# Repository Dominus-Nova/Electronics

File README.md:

# Electronics
a collection of my kicad electronics projects

general note is that this is my shit, its only public so my friends can see it without a github account
oh, new folder contains a currently broken project, it has its own repo but it broke

test^2

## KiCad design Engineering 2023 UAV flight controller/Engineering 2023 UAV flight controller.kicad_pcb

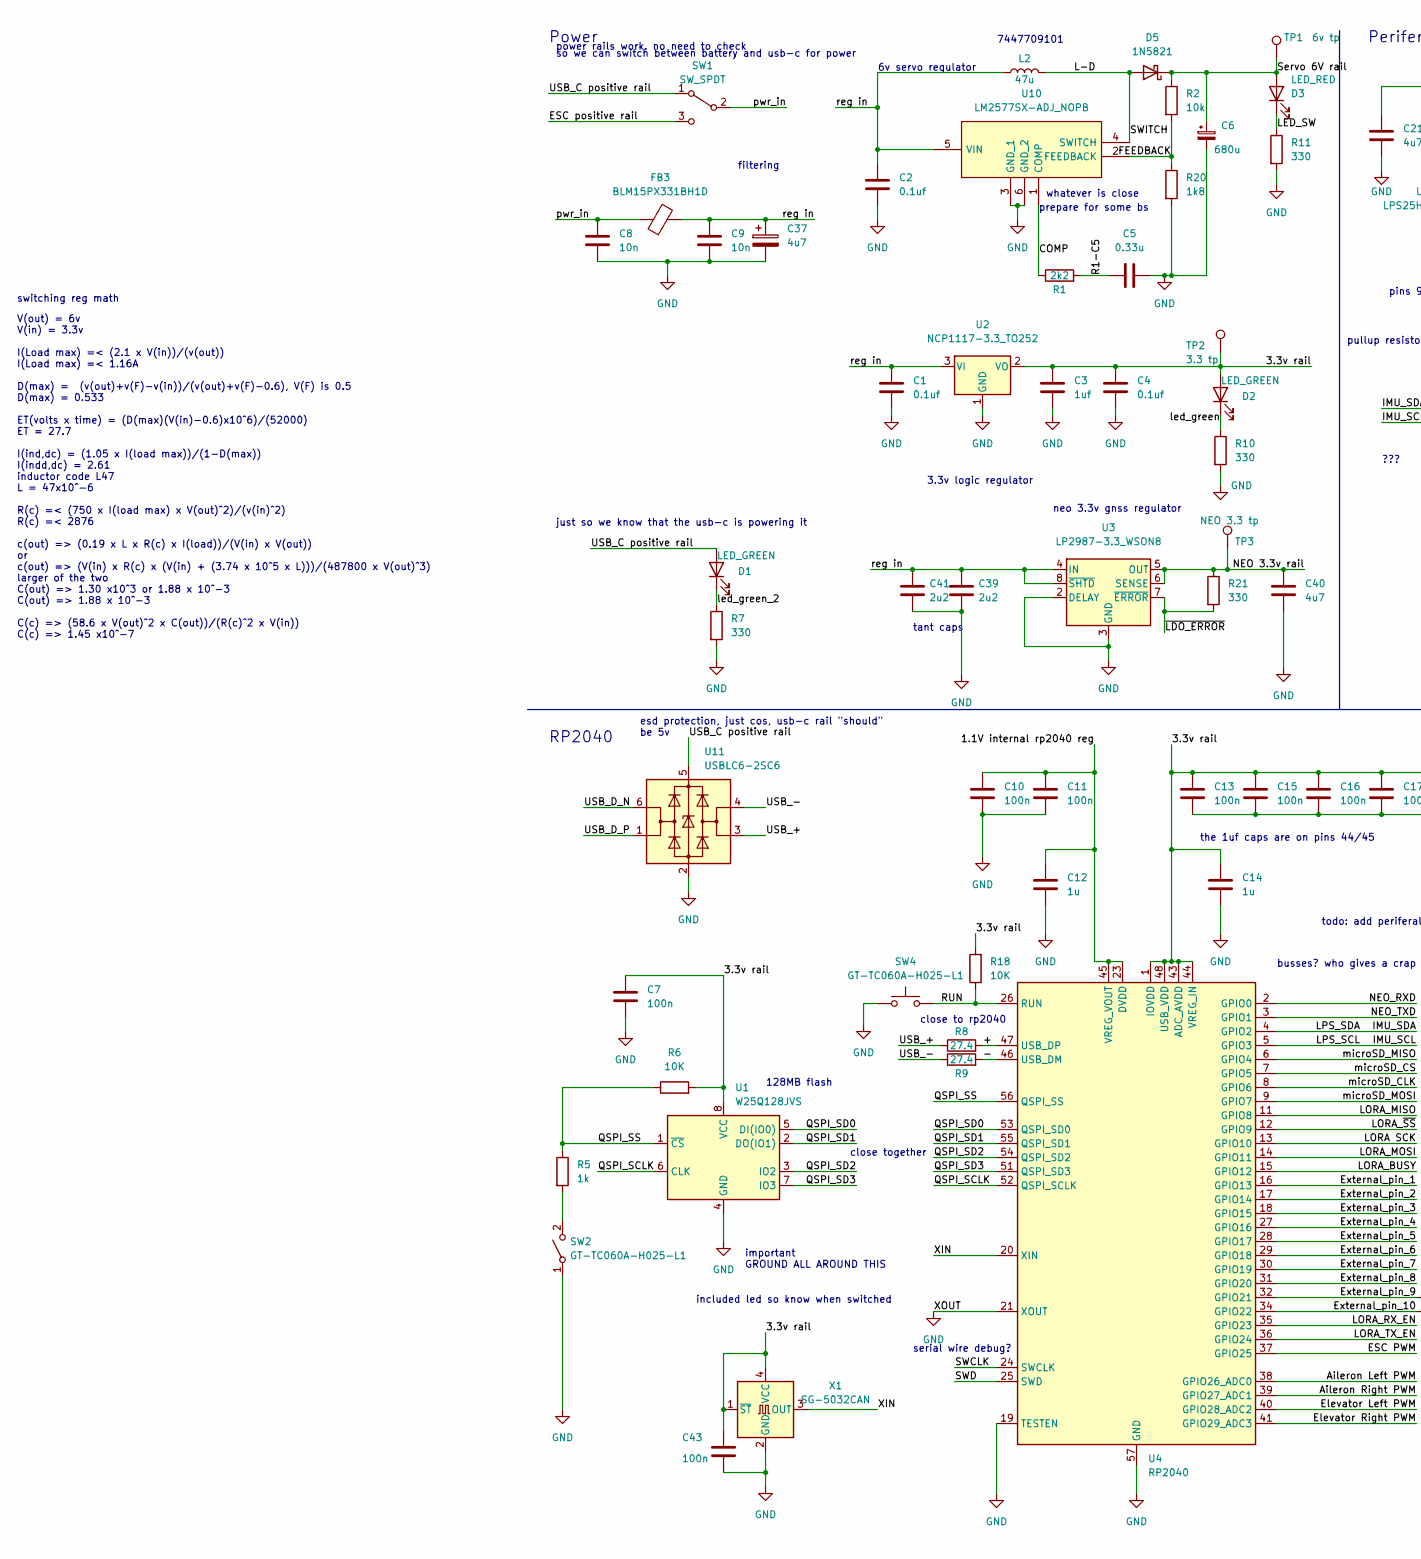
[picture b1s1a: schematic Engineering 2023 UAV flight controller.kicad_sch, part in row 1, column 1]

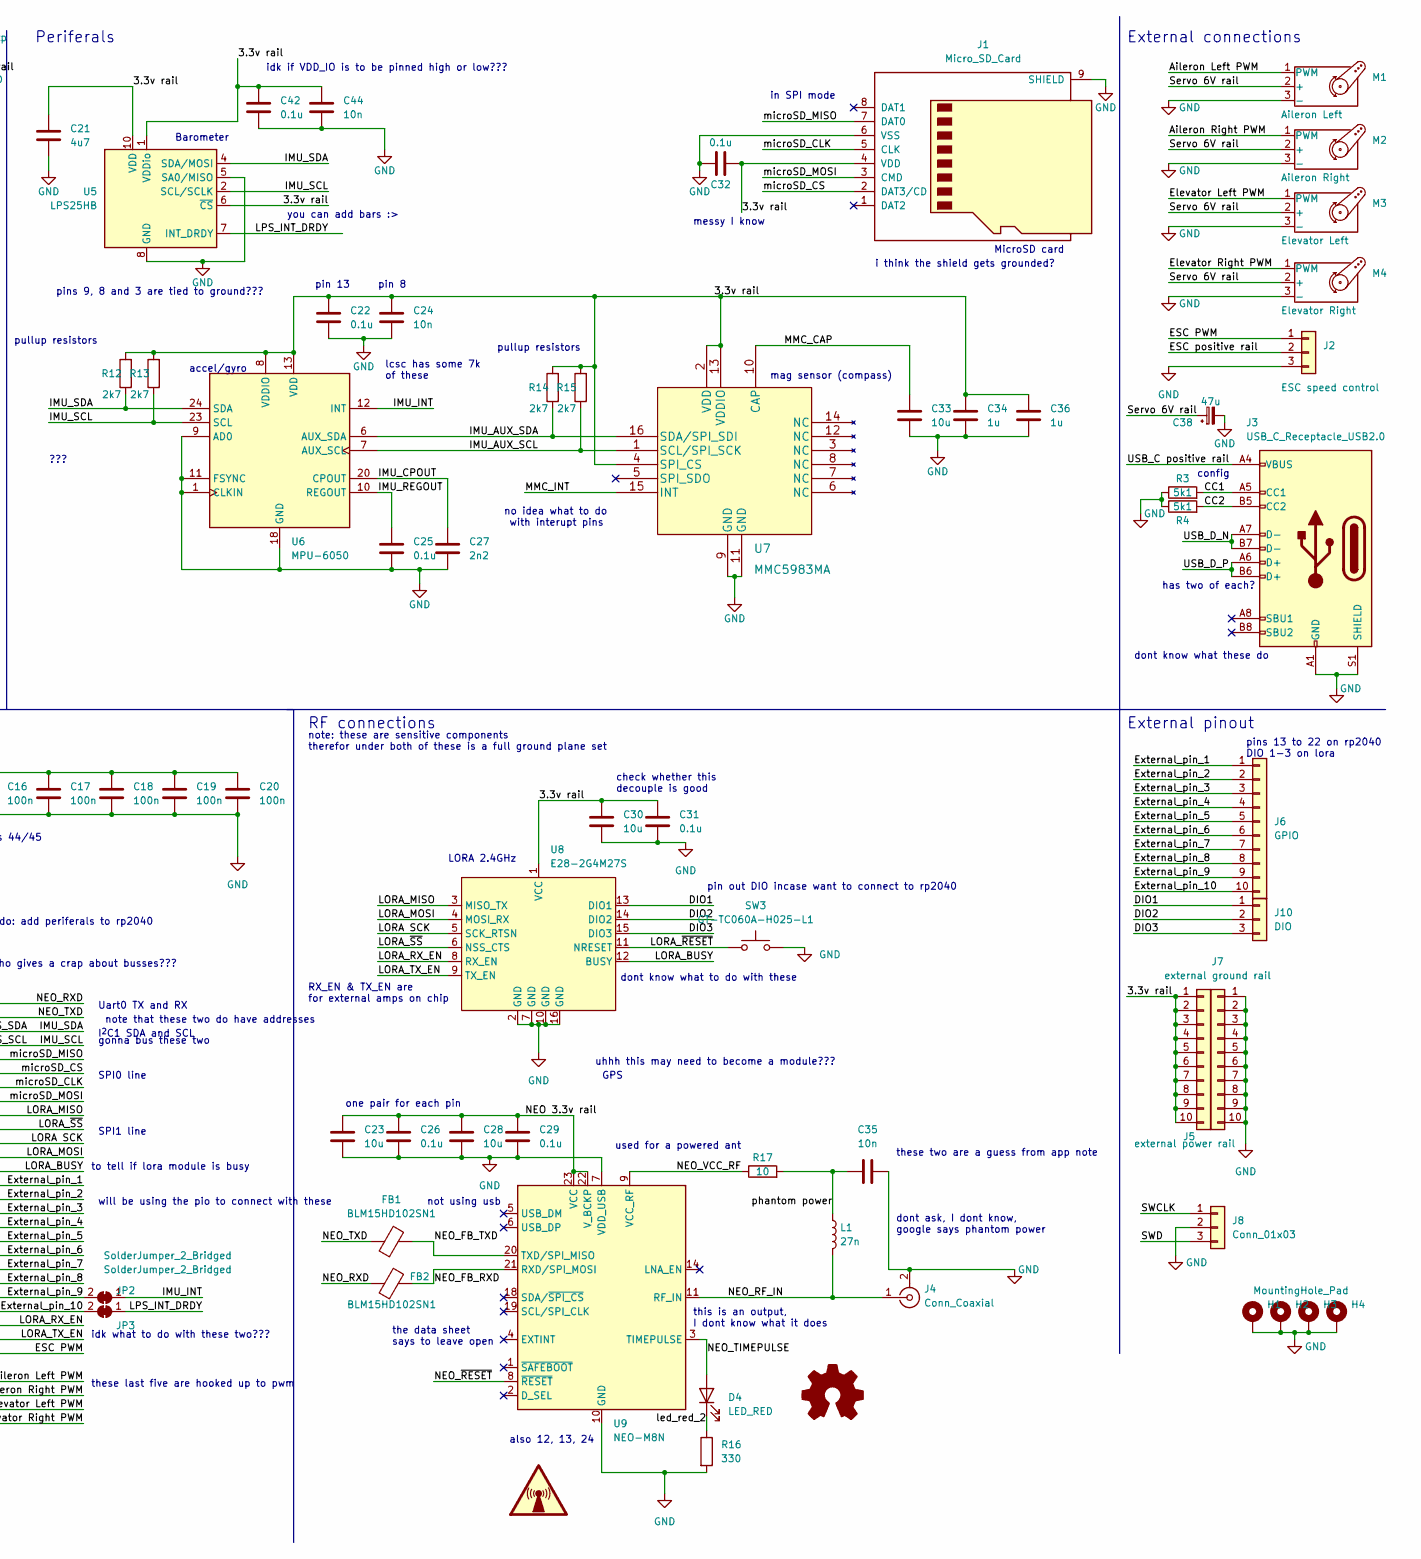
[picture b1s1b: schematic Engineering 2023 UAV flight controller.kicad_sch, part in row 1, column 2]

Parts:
C1, C2, C4: 0.1uf; C_0603_1608Metric
C3: 1uf; C_0603_1608Metric
C5: 0.33u; C_0603_1608Metric
C6: 680u; CP_Elec_8x6.5
C7, C10, C11, C13, C15, C16, C17, C18, C19, C20, C43: 100n; C_0603_1608Metric
C8, C9, C24, C35, C44: 10n; C_0603_1608Metric
C12, C14, C34, C36: 1u; C_0603_1608Metric
C21, C40: 4u7; C_0603_1608Metric
C22, C25, C26, C29, C31, C32, C42: 0.1u; C_0603_1608Metric
C23, C28, C30, C33: 10u; C_0603_1608Metric
C27: 2n2; C_0603_1608Metric
C37: 4u7; CP_Elec_5x3
C38: 47u; CP_Elec_5x3
C39, C41: 2u2; C_0603_1608Metric
D1, D2: LED_GREEN; LED_0603_1608Metric
D3, D4: LED_RED; LED_0603_1608Metric
D5: 1N5821; D_SMC
FB1, FB2: BLM15HD102SN1; L_0402_1005Metric_Pad0.77x0.64mm_HandSolder
FB3: BLM15PX331BH1D; L_0402_1005Metric_Pad0.77x0.64mm_HandSolder
H1, H2, H3, H4: MountingHole_Pad; MountingHole_3.2mm_M3_Pad_Via
J1: Micro_SD_Card; microSD_HC_Hirose_DM3D-SF
J2: ESC speed control; PinHeader_1x03_P2.54mm_Vertical
J3: USB_C_Receptacle_USB2.0; USB_C_Receptacle_JAE_DX07S016JA1R1500
J4: Conn_Coaxial; SMA_Amphenol_901-143_Horizontal
J5: external power rail; PinHeader_1x10_P2.54mm_Vertical
J6: GPIO; PinHeader_1x10_P2.54mm_Vertical
J7: external ground rail; PinHeader_1x10_P2.54mm_Vertical
J8: Conn_01x03; PinHeader_1x03_P2.54mm_Vertical
J10: DIO; PinHeader_1x03_P2.54mm_Vertical
JP2, JP3: SolderJumper_2_Bridged; SolderJumper-2_P1.3mm_Bridged_RoundedPad1.0x1.5mm
L1: 27n; L_0603_1608Metric
L2: 47u; L_Wuerth_WE-PD-Typ-LS
M1: Aileron Left; PinHeader_1x03_P2.54mm_Vertical
M2: Aileron Right; PinHeader_1x03_P2.54mm_Vertical
M3: Elevator Left; PinHeader_1x03_P2.54mm_Vertical
M4: Elevator Right; PinHeader_1x03_P2.54mm_Vertical
R1: 2k2; R_0603_1608Metric
R2: 10k; R_0603_1608Metric
R3, R4: 5k1; R_0603_1608Metric
R5: 1k; R_0603_1608Metric
R6, R18: 10K; R_0603_1608Metric
R7, R10, R11, R16, R21: 330; R_0603_1608Metric
R8, R9: 27.4; R_0603_1608Metric
R12, R13, R14, R15: 2k7; R_0603_1608Metric
R17: 10; R_0603_1608Metric
R20: 1k8; R_0603_1608Metric
SW1: SW_SPDT; SW_SPDT_CK-JS102011SAQN
SW2, SW3, SW4: GT-TC060A-H025-L1; SW_SPST_CK_RS282G05A3
TP1: 6v tp; TestPoint_Pad_D2.5mm
TP2: 3.3 tp; TestPoint_Pad_D2.5mm
TP3: NEO 3.3 tp; TestPoint_Pad_D2.5mm
U1: W25Q128JVS; SOIC-8_5.23x5.23mm_P1.27mm
U2: NCP1117-3.3_TO252; TO-252-2
U3: LP2987-3.3_WSON8; WSON-8-1EP_4x4mm_P0.8mm_EP2.2x3mm
U4: RP2040; QFN-56-1EP_7x7mm_P0.4mm_EP3.2x3.2mm
U5: LPS25HB; ST_HLGA-10_2.5x2.5mm_P0.6mm_LayoutBorder3x2y
U6: MPU-6050; InvenSense_QFN-24_4x4mm_P0.5mm
U7: MMC5983MA
U8: E28-2G4M27S
U9: NEO-M8N; ublox_NEO
U10: LM2577SX-ADJ_NOPB; TO-263-5_TabPin3; Manufacturer_Part_Number LM2577SX-ADJ/NOPB; Mouser Part Number 926-LM2577SXADJNOPB
U11: USBLC6-2SC6; SOT-23-6
X1: SG-5032CAN; Oscillator_SMD_SeikoEpson_SG8002LB-4Pin_5.0x3.2mm

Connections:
/1.1V internal rp2040 reg: C10.1, C11.1, C12.1, U4.23 (DVDD), U4.45 (VREG_VOUT), U4.50 (DVDD)
/3.3v rail: C3.1, C4.1, C7.1, C13.1, C14.1, C15.1, C16.1, C17.1, C18.1, C19.1, C20.1, C21.2, C22.2, C24.2, C30.1, C31.1, C32.1, C34.2, C36.2, C42.2, C43.1, C44.2, D2.2 (A), J1.4 (VDD), J5.1, J5.2, J5.3, J5.4, J5.5, J5.6, J5.7, J5.8, J5.9, J5.10, R6.2, R12.2, R13.2, R14.2, R15.2, R18.2, TP2.1, U1.8 (VCC), U2.2 (VO), U4.1 (IOVDD), U4.10 (IOVDD), U4.22 (IOVDD), U4.33 (IOVDD), U4.42 (IOVDD), U4.43 (ADC_AVDD), U4.44 (VREG_IN), U4.48 (USB_VDD), U4.49 (IOVDD), U5.1 (VDDio), U5.6 (~CS), U5.10 (VDD), U6.8 (VDDIO), U6.13 (VDD), U7.2 (VDD), U7.4 (SPI_CS), U7.13 (VDDIO), U8.1 (VCC), X1.1 (~ST), X1.4 (VCC)
/+: R8.2, U4.47 (USB_DP)
/-: R9.2, U4.46 (USB_DM)
/Aileron Left PWM: M1.1 (PWM), U4.38 (GPIO26_ADC0)
/Aileron Right PWM: M2.1 (PWM), U4.39 (GPIO27_ADC1)
/CC1: J3.A5 (CC1), R3.2
/CC2: J3.B5 (CC2), R4.2
/COMP: R1.1, U10.1 (COMP)
/DIO1: J10.1, U8.13 (DIO1)
/DIO2: J10.2, U8.14 (DIO2)
/DIO3: J10.3, U8.15 (DIO3)
/ESC PWM: J2.1, U4.37 (GPIO25)
/ESC positive rail: J2.2, SW1.3 (C)
/Elevator Left PWM: M3.1 (PWM), U4.40 (GPIO28_ADC2)
/Elevator Right PWM: M4.1 (PWM), U4.41 (GPIO29_ADC3)
/External_pin_1: J6.1, U4.16 (GPIO13)
/External_pin_2: J6.2, U4.17 (GPIO14)
/External_pin_3: J6.3, U4.18 (GPIO15)
/External_pin_4: J6.4, U4.27 (GPIO16)
/External_pin_5: J6.5, U4.28 (GPIO17)
/External_pin_6: J6.6, U4.29 (GPIO18)
/External_pin_7: J6.7, U4.30 (GPIO19)
/External_pin_8: J6.8, U4.31 (GPIO20)
/External_pin_9: J6.9, JP2.2 (B), U4.32 (GPIO21)
/External_pin_10: J6.10, JP3.2 (B), U4.34 (GPIO22)
/FEEDBACK: R2.2, R20.1, U10.2 (FEEDBACK)
/IMU_AUX_SCL: R15.1, U6.7 (AUX_SCL), U7.1 (SCL/SPI_SCK)
/IMU_AUX_SDA: R14.1, U6.6 (AUX_SDA), U7.16 (SDA/SPI_SDI)
/IMU_CPOUT: C27.2, U6.20 (CPOUT)
/IMU_INT: JP2.1 (A), U6.12 (INT)
/IMU_REGOUT: C25.2, U6.10 (REGOUT)
/IMU_SCL: R13.1, U4.5 (GPIO3), U5.2 (SCL/SCLK), U6.23 (SCL)
/IMU_SDA: R12.1, U4.4 (GPIO2), U5.4 (SDA/MOSI), U6.24 (SDA)
/L-D: D5.2 (A), L2.2, U10.4 (SWITCH)
/LED_SW: D3.1 (K), R11.1
/LORA SCK: U4.13 (GPIO10), U8.5 (SCK_RTSN)
/LORA_BUSY: U4.15 (GPIO12), U8.12 (BUSY)
/LORA_MISO: U4.11 (GPIO8), U8.3 (MISO_TX)
/LORA_MOSI: U4.14 (GPIO11), U8.4 (MOSI_RX)
/LORA_RX_EN: U4.35 (GPIO23), U8.8 (RX_EN)
/LORA_TX_EN: U4.36 (GPIO24), U8.9 (TX_EN)
/LORA_~RESET: SW3.1, U8.11 (NRESET)
/LORA_~SS: U4.12 (GPIO9), U8.6 (NSS_CTS)
/LPS_INT_DRDY: JP3.1 (A), U5.7 (INT_DRDY)
/MMC_CAP: C33.2, U7.10 (CAP)
/MMC_INT: U7.15 (INT)
/NEO 3.3v rail: C23.1, C26.1, C28.1, C29.1, C40.1, R21.1, TP3.1, U3.5 (OUT), U3.6 (SENSE), U9.22 (V_BCKP), U9.23 (VCC)
/NEO_FB_RXD: FB2.2, U9.21 (RXD/SPI_MOSI)
/NEO_FB_TXD: FB1.2, U9.20 (TXD/SPI_MISO)
/NEO_RF_IN: J4.1 (In), L1.2, U9.11 (RF_IN)
/NEO_RXD: FB2.1, U4.2 (GPIO0)
/NEO_TIMEPULSE: D4.2 (A), U9.3 (TIMEPULSE)
/NEO_TXD: FB1.1, U4.3 (GPIO1)
/NEO_VCC_RF: R17.1, U9.9 (VCC_RF)
/NEO_~RESET: U9.8 (~RESET)
/QSPI_SCLK: U1.6 (CLK), U4.52 (QSPI_SCLK)
/QSPI_SD0: U1.5 (DI(IO0)), U4.53 (QSPI_SD0)
/QSPI_SD1: U1.2 (DO(IO1)), U4.55 (QSPI_SD1)
/QSPI_SD2: U1.3 (IO2), U4.54 (QSPI_SD2)
/QSPI_SD3: U1.7 (IO3), U4.51 (QSPI_SD3)
/QSPI_SS: R5.1, R6.1, U1.1 (~CS), U4.56 (QSPI_SS)
/R1-C5: C5.1, R1.2
/RUN: R18.1, SW4.2, U4.26 (RUN)
/SWCLK: J8.1, U4.24 (SWCLK)
/SWD: J8.3, U4.25 (SWD)
/Servo 6V rail: C6.1, C38.1, D3.2 (A), D5.1 (K), M1.2 (+), M2.2 (+), M3.2 (+), M4.2 (+), R2.1, TP1.1
/USB_+: R8.1, U11.3 (I/O2)
/USB_-: R9.1, U11.4 (I/O2)
/USB_C positive rail: D1.2 (A), J3.A4 (VBUS), J3.A9 (VBUS), J3.B4 (VBUS), J3.B9 (VBUS), SW1.1 (A), U11.5 (VBUS)
/USB_D_N: J3.A7 (D-), J3.B7 (D-), U11.6 (I/O1)
/USB_D_P: J3.A6 (D+), J3.B6 (D+), U11.1 (I/O1)
/XIN: U4.20 (XIN), X1.3 (OUT)
/led_green: D2.1 (K), R10.1
/led_green_2: D1.1 (K), R7.1
/led_red_2: D4.1 (K), R16.1
/microSD_CLK: J1.5 (CLK), U4.8 (GPIO6)
/microSD_CS: J1.2 (DAT3/CD), U4.7 (GPIO5)
/microSD_MISO: J1.7 (DAT0), U4.6 (GPIO4)
/microSD_MOSI: J1.3 (CMD), U4.9 (GPIO7)
/phantom power: C35.1, L1.1, R17.2
/pwr_in: C8.1, FB3.1, SW1.2 (B)
/reg in: C1.1, C2.1, C9.1, C37.1, C39.1, C41.1, FB3.2, L2.1, U2.3 (VI), U3.4 (IN), U3.8 (~SHTD), U10.5 (VIN)
/~LDO_ERROR: R21.2, U3.7 (~ERROR)
GND: C1.2, C2.2, C3.2, C4.2, C5.2, C6.2, C7.2, C8.2, C9.2, C10.2, C11.2, C12.2, C13.2, C14.2, C15.2, C16.2, C17.2, C18.2, C19.2, C20.2, C21.1, C22.1, C23.2, C24.1, C25.1, C26.2, C27.1, C28.2, C29.2, C30.2, C31.2, C32.2, C33.1, C34.1, C35.2, C36.1, C37.2, C38.2, C39.2, C40.2, C41.2, C42.1, C43.2, C44.1, H1.1, H2.1, H3.1, H4.1, J1.6 (VSS), J1.9 (SHIELD), J2.3, J3.A1 (GND), J3.A12 (GND), J3.B1 (GND), J3.B12 (GND), J3.S1 (SHIELD), J4.2 (Ext), J7.1, J7.2, J7.3, J7.4, J7.5, J7.6, J7.7, J7.8, J7.9, J7.10, J8.2, M1.3 (-), M2.3 (-), M3.3 (-), M4.3 (-), R3.1, R4.1, R7.2, R10.2, R11.2, R16.2, R20.2, SW2.1 (A), SW3.2, SW4.1, U1.4 (GND), U2.1 (GND), U3.2 (DELAY), U3.3 (GND), U3.9 (GND), U4.19 (TESTEN), U4.21 (XOUT), U4.57 (GND), U5.3 (GND), U5.5 (SA0/MISO), U5.8 (GND), U5.9 (GND), U6.1 (CLKIN), U6.9 (AD0), U6.11 (FSYNC), U6.18 (GND), U7.9 (GND), U7.11 (GND), U8.2 (GND), U8.7 (GND), U8.10 (GND), U8.16 (GND), U9.7 (VDD_USB), U9.10 (GND), U9.12 (GND), U9.13 (GND), U9.24 (GND), U10.3 (GND_1), U10.6 (GND_2), U11.2 (GND), X1.2 (GND)
unnamed: R5.2, SW2.2 (B)

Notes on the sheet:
lcsc has some 7k of these
you can add bars :>
pullup resistors
todo: add periferals to rp2040
note: these are sensitive components therefor under both of these is a full ground plane set
esd protection, just cos, usb-c rail "should" be 5v
RF connections
this is an output, I dont know what it does
not using usb
important GROUND ALL AROUND THIS
External pinout
has two of each?
config
close together
idk what to do with these two???
pin out DIO incase want to connect to rp2040
these last five are hooked up to pwm
pins 9, 8 and 3 are tied to ground???
mag sensor (compass)
128MB flash
3.3v logic regulator
will be using the pio to connect with these
i think the shield gets grounded?
switching reg math
to tell if lora module is busy
prepare for some bs
pin 13
power rails work. no need to check
Uart0 TX and RX
Power
???
no idea what to do with interupt pins
Periferals
so we can switch between battery and usb-c for power
LORA 2.4GHz
the data sheet says to leave open
check whether this decouple is good
idk if VDD_IO is to be pinned high or low???
dont ask, I dont know, google says phantom power
pin 8

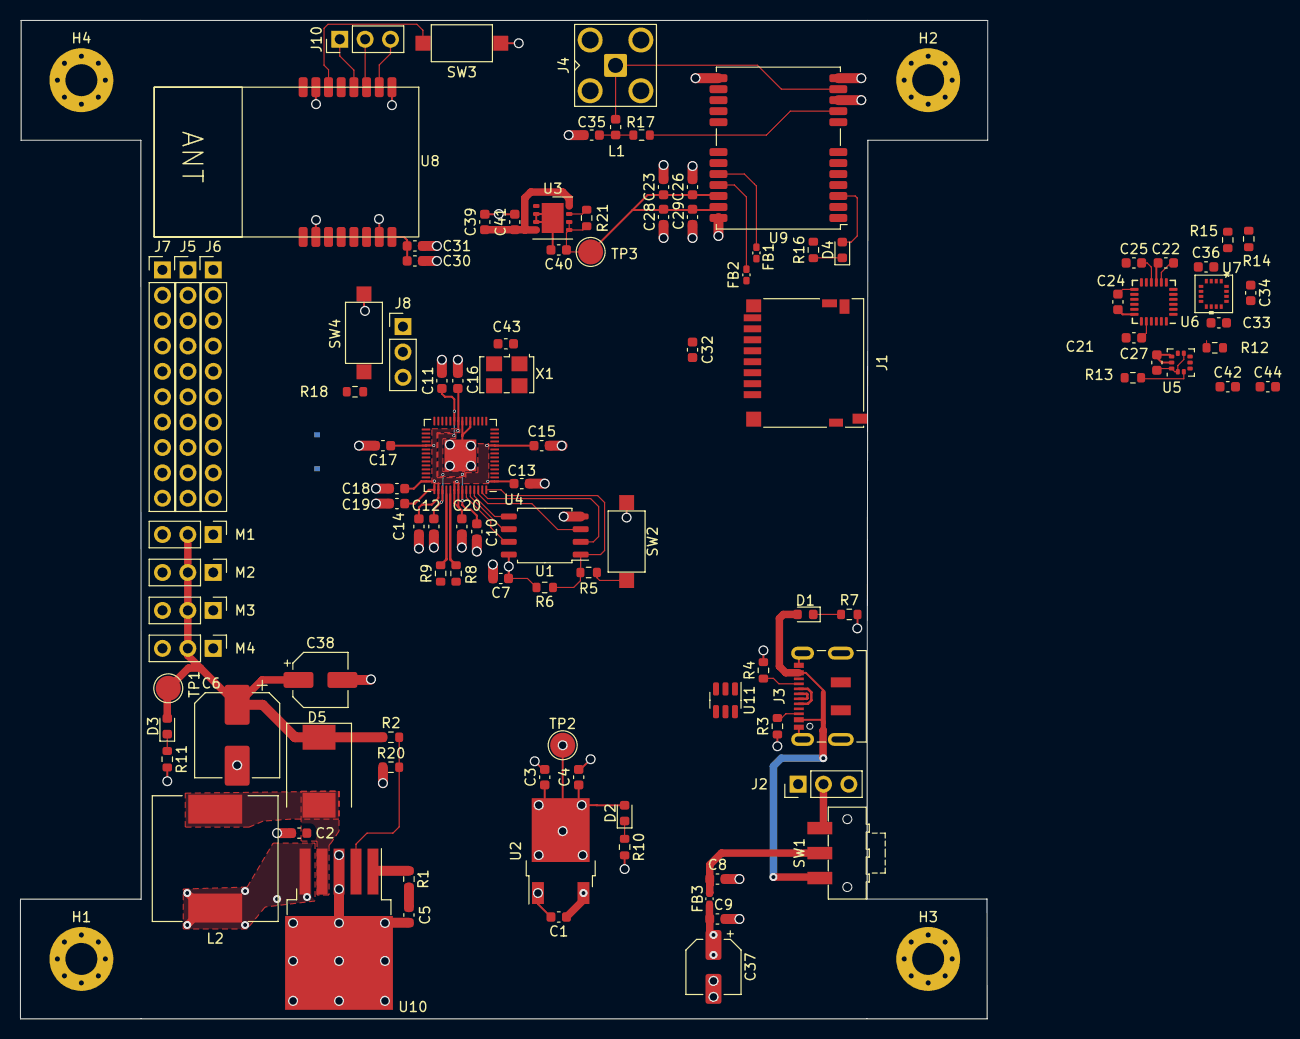
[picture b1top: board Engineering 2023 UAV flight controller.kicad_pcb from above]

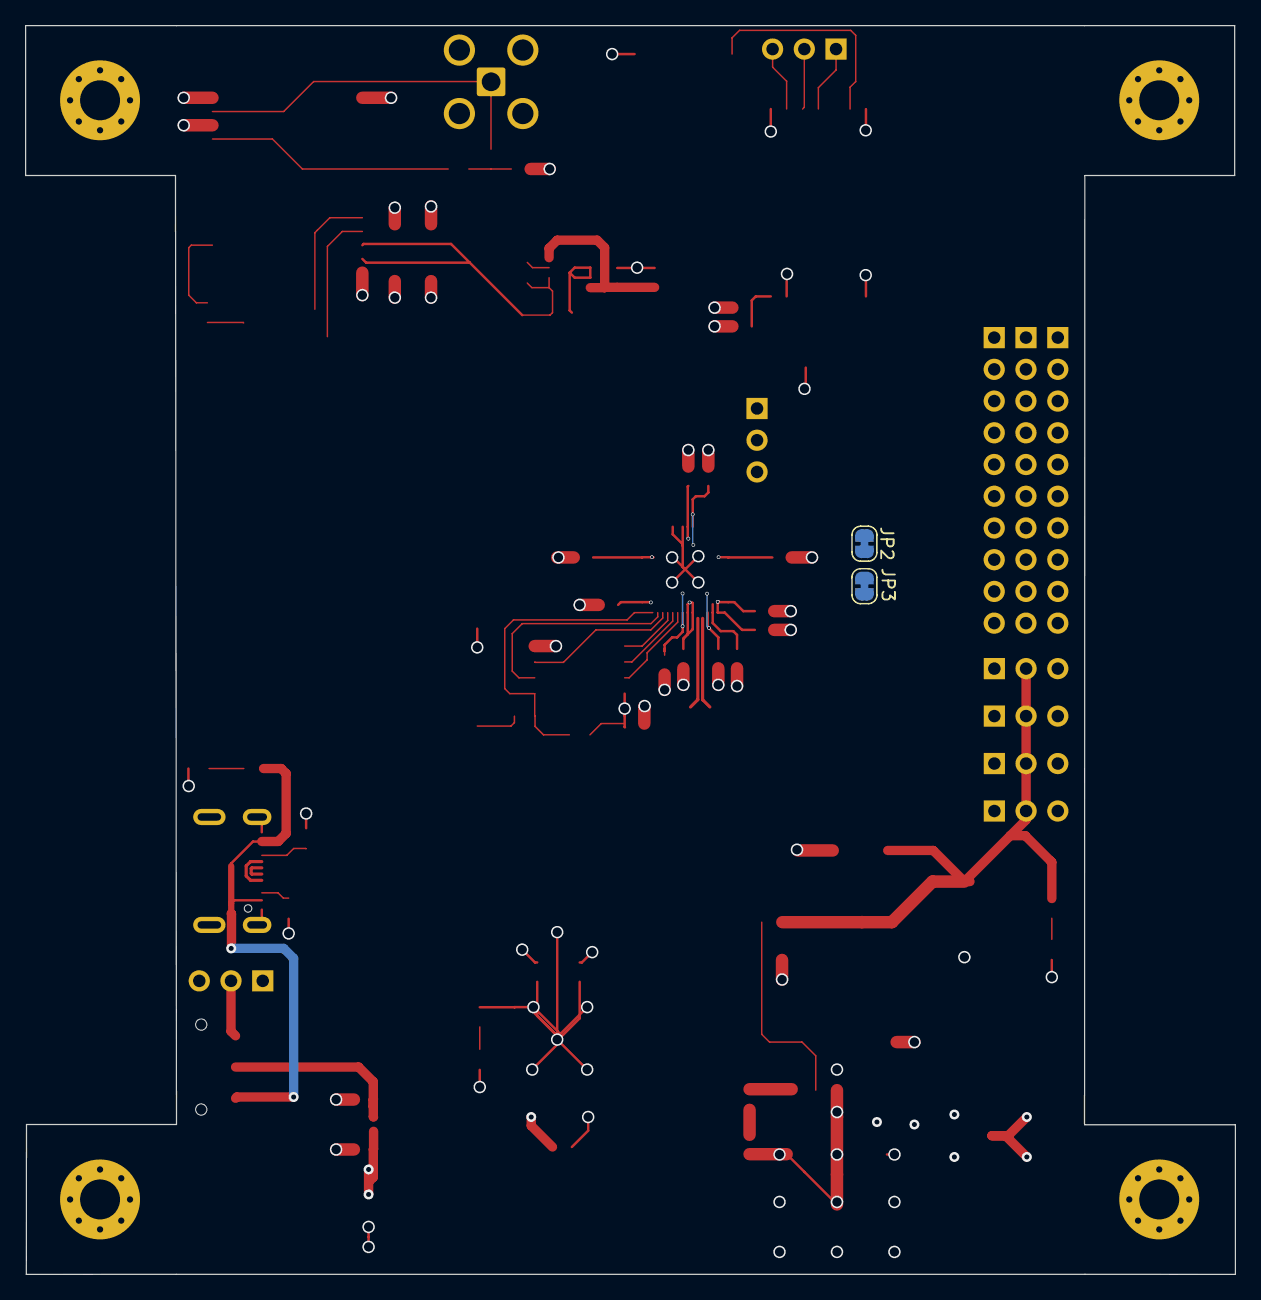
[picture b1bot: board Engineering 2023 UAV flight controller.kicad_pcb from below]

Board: 4 copper layers, 96.9 x 100.0 mm, 112 parts (2 on the bottom side), 84 nets.

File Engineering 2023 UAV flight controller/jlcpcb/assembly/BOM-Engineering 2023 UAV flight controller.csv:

Comment,Designator,Footprint,LCSC
10n,"C24,C35",C_0603_1608Metric,C100042
5k1,"R3,R4",R_0603_1608Metric,C105580
330,"R10,R11,R16,R20,R21,R6,R7",R_0603_1608Metric,C105881
10,R17,R_0603_1608Metric,C109317
1K2,R2,R_0603_1608Metric,C114605
2k7,"R12,R13,R14,R15,R18,R19",R_0603_1608Metric,C114612
2k2,R1,R_0603_1608Metric,C114662
0.1uf,"C1,C2,C4",C_0603_1608Metric,C122538
100n,"C10,C11,C13,C15,C16,C17,C18,C19,C20,C22,C25,C26,C29,C31,C32,C37,C7",C_0603_1608Metric,C14663
1u,"C12,C14,C3,C34,C36",C_0603_1608Metric,C14664
NCP1117-3.3_TO252,U2,TO-252-2,C152529
LM2577SX-ADJ_NOPB,"IC1,U5",TO-263-5_TabPin3,C17117
27.4,"R8,R9",R_0603_1608Metric,C185346
LED_RED,"D3,D4",LED_0603_1608Metric,C188726
LED_GREEN,"D1,D2",LED_0603_1608Metric,C188729
RP2040,U4,QFN-56-1EP_7x7mm_P0.4mm_EP3.2x3.2mm,C2040
 BLM15HD102SN1,"FB1,FB2",L_0402_1005Metric_Pad0.77x0.64mm_HandSolder,C21516
SW_SPDT,SW1,SW_SPDT_CK-JS102011SAQN,C221660
1k,R5,R_0603_1608Metric,C22548
SW_Push,SW3,SW_SPST_Omron_B3FS-100xP,C231324
MPU-6050,U6,InvenSense_QFN-24_4x4mm_P0.5mm,C24112
2u2,"C39,C41",C_0603_1608Metric,C309478
2n2,C27,C_0603_1608Metric,C309517
10u,"C23,C28,C30,C33",C_0603_1608Metric,C326057
4u7,"C21,C40",C_0603_1608Metric,C326580
27p,"C8,C9",C_0603_1608Metric,C107045
W25Q128JVS,U1,SOIC-8_5.23x5.23mm_P1.27mm,C97521
27n,L1,L_0603_1608Metric,C98072
Micro_SD_Card,J1,microSD_HC_Hirose_DM3D-SF,
MMC5983MA,U7,MMC5983MA,
Conn_Coaxial,J4,SMA_Amphenol_901-143_Horizontal,
E28-2G4M27S,U8,E28-2G4M27S,
Elevator Left,M3,PinHeader_1x03_P2.54mm_Vertical,
0.33u,C5,C_0603_1608Metric,
external ground rail,J7,PinHeader_1x10_P2.54mm_Vertical,
Aileron Left,M1,PinHeader_1x03_P2.54mm_Vertical,
SolderJumper_2_Bridged,JP1,SolderJumper-2_P1.3mm_Bridged_RoundedPad1.0x1.5mm,
Elevator Right,M4,PinHeader_1x03_P2.54mm_Vertical,
NEO-M8N,U9,ublox_NEO,
4FSH922,SW2,SW_MEC_5GSH9,
GPIO,J6,PinHeader_1x10_P2.54mm_Vertical,
ESC speed control,J2,PinHeader_1x03_P2.54mm_Vertical,
Aileron Right,M2,PinHeader_1x03_P2.54mm_Vertical,
LP2987-3.3_WSON8,U3,WSON-8-1EP_4x4mm_P0.8mm_EP2.2x3mm,
USB_C_Receptacle_USB2.0,J3,USB_C_Receptacle_JAE_DX07S016JA1R1500,
external power rail,J5,PinHeader_1x10_P2.54mm_Vertical,
ABLS-12.000MHZ-B4-T,Y1,Crystal_SMD_HC49-SD,
680u,C6,CP_Elec_8x6.5,
Serial wire debug,J8,PinHeader_1x02_P2.54mm_Vertical,
MountingHole_Pad,H2,MountingHole_3.2mm_M3_Pad_Via,
MountingHole_Pad,H1,MountingHole_3.2mm_M3_Pad_Via,
MountingHole_Pad,H4,MountingHole_3.2mm_M3_Pad_Via,
47u,L2,L_Wuerth_WE-PD-Typ-LS,
1N5821,D5,D_SMC,
6v tp,TP1,TestPoint_Pad_D2.5mm,
MountingHole_Pad,H3,MountingHole_3.2mm_M3_Pad_Via,
reset short?,J9,PinHeader_1x02_P2.54mm_Vertical,
3.3 tp,TP2,TestPoint_Pad_D2.5mm,
47u,C38,CP_Elec_5x3,
DIO,J10,PinHeader_1x03_P2.54mm_Vertical,
NEO 3.3 tp,TP3,TestPoint_Pad_D2.5mm,

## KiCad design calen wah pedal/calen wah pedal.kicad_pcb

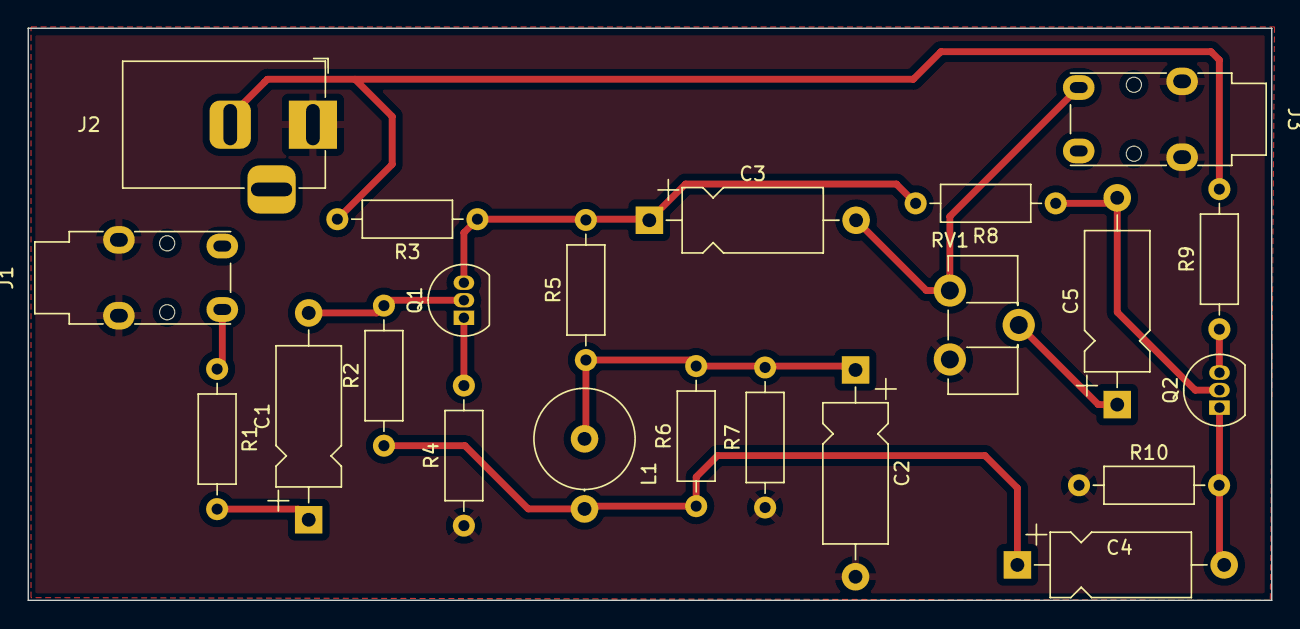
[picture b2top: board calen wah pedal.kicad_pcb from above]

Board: 2 copper layers, 90.2 x 41.5 mm, 22 parts (0 on the bottom side), 14 nets.

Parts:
C1, C4: 0.01u; CP_Axial_L10.0mm_D4.5mm_P15.00mm_Horizontal
C2: 4u7; CP_Axial_L10.0mm_D4.5mm_P15.00mm_Horizontal
C3, C5: 0.22u; CP_Axial_L10.0mm_D4.5mm_P15.00mm_Horizontal
J1: in; Jack_3.5mm_Lumberg_1503_07_Horizontal
J2: 9v in; BarrelJack_Horizontal
J3: out; Jack_3.5mm_Lumberg_1503_07_Horizontal
L1: 500m; L_Axial_L24.0mm_D7.1mm_P5.08mm_Vertical_Vishay_IM-10-28
Q1, Q2: 2N3904; TO-92_Inline
R1: 68k; R_Axial_DIN0207_L6.3mm_D2.5mm_P10.16mm_Horizontal
R2: 1k5; R_Axial_DIN0207_L6.3mm_D2.5mm_P10.16mm_Horizontal
R3: 22k; R_Axial_DIN0207_L6.3mm_D2.5mm_P10.16mm_Horizontal
R4: 470; R_Axial_DIN0207_L6.3mm_D2.5mm_P10.16mm_Horizontal
R5, R8: 470k; R_Axial_DIN0207_L6.3mm_D2.5mm_P10.16mm_Horizontal
R6: 33k; R_Axial_DIN0207_L6.3mm_D2.5mm_P10.16mm_Horizontal
R7: 82k; R_Axial_DIN0207_L6.3mm_D2.5mm_P10.16mm_Horizontal
R9: 1k; R_Axial_DIN0207_L6.3mm_D2.5mm_P10.16mm_Horizontal
R10: 10k; R_Axial_DIN0207_L6.3mm_D2.5mm_P10.16mm_Horizontal
RV1: 100k; Potentiometer_ACP_CA9-H5_Horizontal

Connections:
/9V: J2.2, R3.2, R9.2
GND: C2.2, J1.T, J2.1, J3.T, R4.1, R7.1, R10.1, RV1.3
unnamed: C1.1, R1.2
unnamed: C1.2, Q1.2 (B), R2.2
unnamed: C2.1, L1.1, R5.1, R6.2, R7.2
unnamed: C3.1, Q1.3 (C), R3.1, R5.2, R8.2
unnamed: C3.2, J3.S, RV1.1
unnamed: C4.1, L1.2, R2.1, R6.1
unnamed: C4.2, Q2.1 (E), R10.2
unnamed: C5.1, RV1.2
unnamed: C5.2, Q2.2 (B), R8.1
unnamed: J1.S, R1.1
unnamed: Q1.1 (E), R4.2
unnamed: Q2.3 (C), R9.1

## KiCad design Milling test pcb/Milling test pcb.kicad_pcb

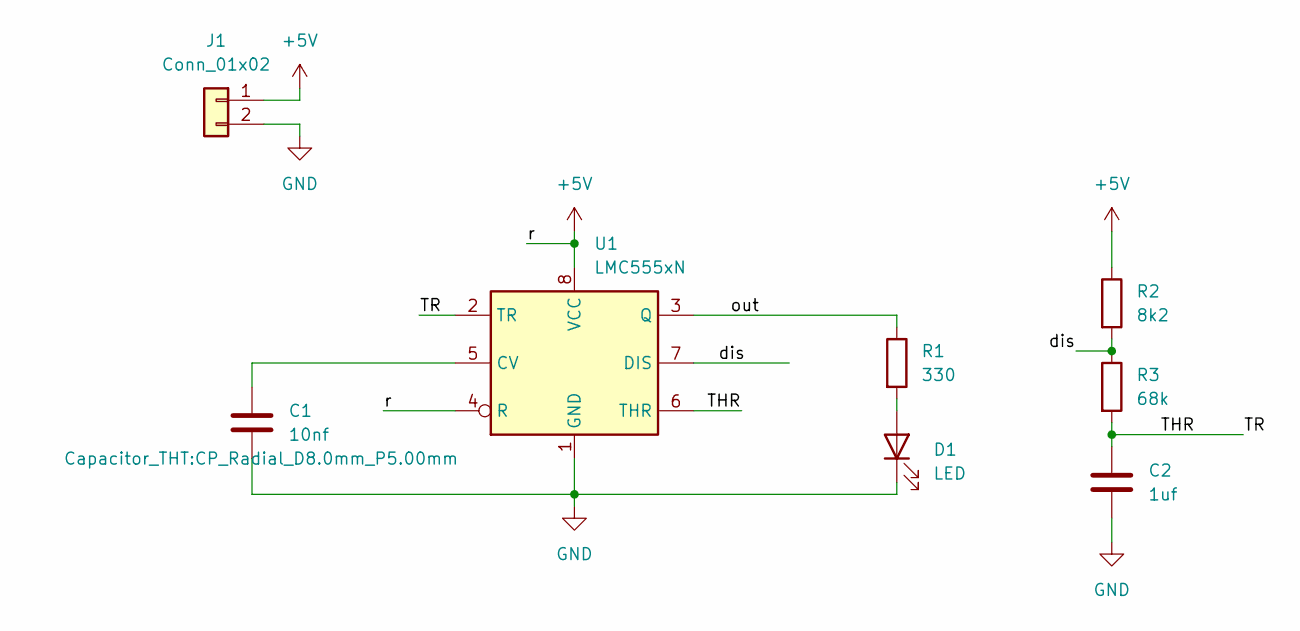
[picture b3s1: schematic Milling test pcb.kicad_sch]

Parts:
C1: 10nf; CP_Radial_D8.0mm_P5.00mm
C2: 1uf; CP_Radial_D8.0mm_P5.00mm
D1: LED; LED_D3.0mm
J1: Conn_01x02; PinHeader_1x02_P2.54mm_Vertical
R1: 330; R_Axial_DIN0309_L9.0mm_D3.2mm_P12.70mm_Horizontal
R2: 8k2; R_Axial_DIN0309_L9.0mm_D3.2mm_P12.70mm_Horizontal
R3: 68k; R_Axial_DIN0309_L9.0mm_D3.2mm_P12.70mm_Horizontal
U1: LMC555xN; DIP-8_W7.62mm

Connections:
+5V: J1.1, R2.1, U1.4 (R), U1.8 (VCC)
/THR: C2.1, R3.2, U1.2 (TR), U1.6 (THR)
/dis: R2.2, R3.1, U1.7 (DIS)
/out: R1.1, U1.3 (Q)
GND: C1.2, C2.2, D1.1 (K), J1.2, U1.1 (GND)
unnamed: C1.1, U1.5 (CV)
unnamed: D1.2 (A), R1.2

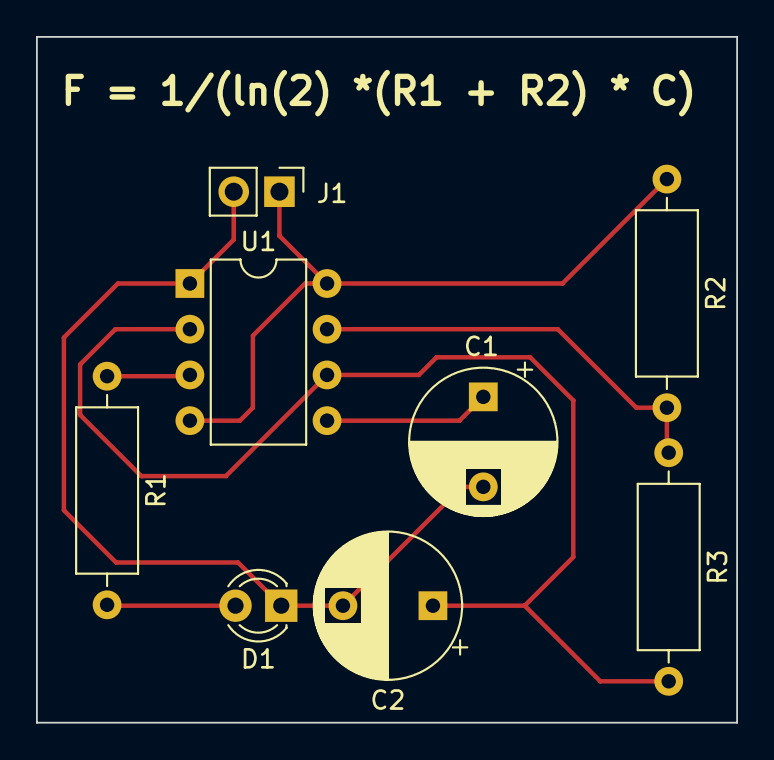
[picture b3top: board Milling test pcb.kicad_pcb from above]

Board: 2 copper layers, 38.9 x 38.1 mm, 8 parts (0 on the bottom side), 7 nets.

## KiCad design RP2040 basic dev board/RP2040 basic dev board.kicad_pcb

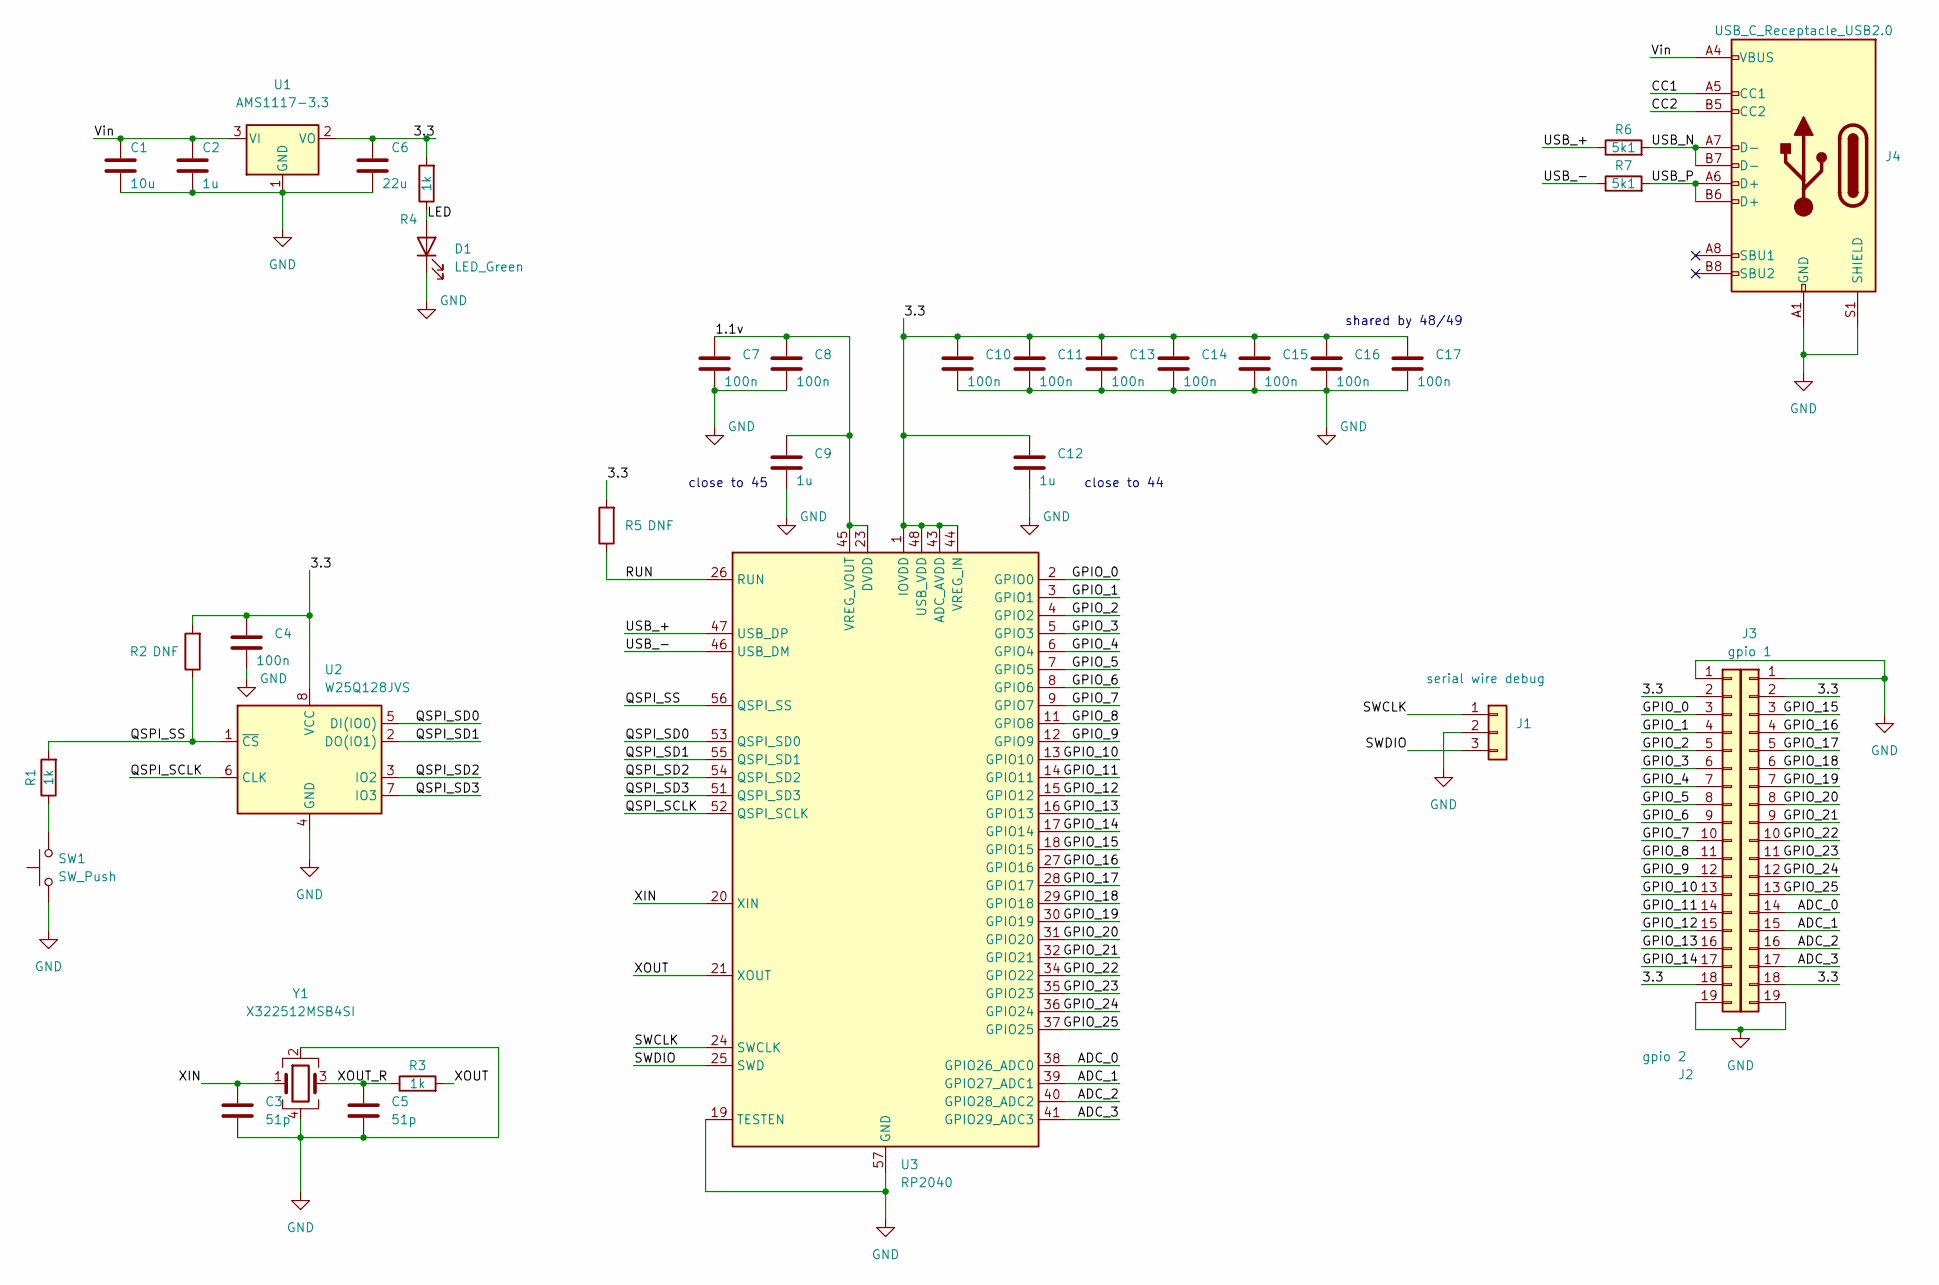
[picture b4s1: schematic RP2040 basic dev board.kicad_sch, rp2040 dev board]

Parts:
C1: 10u; C_0603_1608Metric
C2, C9, C12: 1u; C_0603_1608Metric
C3, C5: 51p; C_0603_1608Metric
C4, C7, C8, C10, C11, C13, C14, C15, C16, C17: 100n; C_0603_1608Metric
C6: 22u; C_0603_1608Metric
D1: LED_Green; LED_0603_1608Metric
J1: serial wire debug; PinSocket_1x03_P2.54mm_Vertical
J2: gpio 2; PinSocket_1x19_P2.54mm_Vertical
J3: gpio 1; PinSocket_1x19_P2.54mm_Vertical
J4: USB_C_Receptacle_USB2.0; USB_C_Receptacle_JAE_DX07S016JA1R1500
R1, R3, R4: 1k; R_0603_1608Metric
R2, R5: DNF; R_0603_1608Metric
R6, R7: 5k1; R_0603_1608Metric
SW1: SW_Push; SW_TH_Tactile_Omron_B3F-10xx
U1: AMS1117-3.3; SOT-223-3_TabPin2
U2: W25Q128JVS; SOIC-8_5.23x5.23mm_P1.27mm
U3: RP2040; QFN-56-1EP_7x7mm_P0.4mm_EP3.2x3.2mm
Y1: X322512MSB4SI; Crystal_SMD_3225-4Pin_3.2x2.5mm_HandSoldering

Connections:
/1.1v: C7.1, C8.1, C9.1, U3.23 (DVDD), U3.45 (VREG_VOUT), U3.50 (DVDD)
/3.3: C4.1, C6.1, C10.1, C11.1, C12.1, C13.1, C14.1, C15.1, C16.1, C17.1, J2.2, J2.18, J3.2, J3.18, R2.2, R4.2, R5.2, U1.2 (VO), U2.8 (VCC), U3.1 (IOVDD), U3.10 (IOVDD), U3.22 (IOVDD), U3.33 (IOVDD), U3.42 (IOVDD), U3.43 (ADC_AVDD), U3.44 (VREG_IN), U3.48 (USB_VDD), U3.49 (IOVDD)
/ADC_0: J3.14, U3.38 (GPIO26_ADC0)
/ADC_1: J3.15, U3.39 (GPIO27_ADC1)
/ADC_2: J3.16, U3.40 (GPIO28_ADC2)
/ADC_3: J3.17, U3.41 (GPIO29_ADC3)
/CC1: J4.A5 (CC1)
/CC2: J4.B5 (CC2)
/GPIO_0: J2.3, U3.2 (GPIO0)
/GPIO_1: J2.4, U3.3 (GPIO1)
/GPIO_2: J2.5, U3.4 (GPIO2)
/GPIO_3: J2.6, U3.5 (GPIO3)
/GPIO_4: J2.7, U3.6 (GPIO4)
/GPIO_5: J2.8, U3.7 (GPIO5)
/GPIO_6: J2.9, U3.8 (GPIO6)
/GPIO_7: J2.10, U3.9 (GPIO7)
/GPIO_8: J2.11, U3.11 (GPIO8)
/GPIO_9: J2.12, U3.12 (GPIO9)
/GPIO_10: J2.13, U3.13 (GPIO10)
/GPIO_11: J2.14, U3.14 (GPIO11)
/GPIO_12: J2.15, U3.15 (GPIO12)
/GPIO_13: J2.16, U3.16 (GPIO13)
/GPIO_14: J2.17, U3.17 (GPIO14)
/GPIO_15: J3.3, U3.18 (GPIO15)
/GPIO_16: J3.4, U3.27 (GPIO16)
/GPIO_17: J3.5, U3.28 (GPIO17)
/GPIO_18: J3.6, U3.29 (GPIO18)
/GPIO_19: J3.7, U3.30 (GPIO19)
/GPIO_20: J3.8, U3.31 (GPIO20)
/GPIO_21: J3.9, U3.32 (GPIO21)
/GPIO_22: J3.10, U3.34 (GPIO22)
/GPIO_23: J3.11, U3.35 (GPIO23)
/GPIO_24: J3.12, U3.36 (GPIO24)
/GPIO_25: J3.13, U3.37 (GPIO25)
/LED: D1.2 (A), R4.1
/QSPI_SCLK: U2.6 (CLK), U3.52 (QSPI_SCLK)
/QSPI_SD0: U2.5 (DI(IO0)), U3.53 (QSPI_SD0)
/QSPI_SD1: U2.2 (DO(IO1)), U3.55 (QSPI_SD1)
/QSPI_SD2: U2.3 (IO2), U3.54 (QSPI_SD2)
/QSPI_SD3: U2.7 (IO3), U3.51 (QSPI_SD3)
/QSPI_SS: R1.2, R2.1, U2.1 (~CS), U3.56 (QSPI_SS)
/RUN: R5.1, U3.26 (RUN)
/SWCLK: J1.1, U3.24 (SWCLK)
/SWDIO: J1.3, U3.25 (SWD)
/USB_+: R6.1, U3.47 (USB_DP)
/USB_-: R7.1, U3.46 (USB_DM)
/USB_N: J4.A7 (D-), J4.B7 (D-), R6.2
/USB_P: J4.A6 (D+), J4.B6 (D+), R7.2
/Vin: C1.1, C2.1, J4.A4 (VBUS), J4.A9 (VBUS), J4.B4 (VBUS), J4.B9 (VBUS), U1.3 (VI)
/XIN: C3.1, U3.20 (XIN), Y1.1
/XOUT: R3.2, U3.21 (XOUT)
/XOUT_R: C5.1, R3.1, Y1.3
GND: C1.2, C2.2, C3.2, C4.2, C5.2, C6.2, C7.2, C8.2, C9.2, C10.2, C11.2, C12.2, C13.2, C14.2, C15.2, C16.2, C17.2, D1.1 (K), J1.2, J2.1, J2.19, J3.1, J3.19, J4.A1 (GND), J4.A12 (GND), J4.B1 (GND), J4.B12 (GND), J4.S1 (SHIELD), SW1.1, U1.1 (GND), U2.4 (GND), U3.19 (TESTEN), U3.57 (GND), Y1.2, Y1.4
unnamed: R1.1, SW1.2

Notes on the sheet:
close to 44
shared by 48/49
close to 45
